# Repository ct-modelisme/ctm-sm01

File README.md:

# CTM-SM01: Servo-Motors decoder

The CTM-SM01 is a servo-motors electronic controller for modelrailway projects.
This electronic card is compatible with DCC & AC/DC train layouts.

## Licenses

The hardware is released under OpenHardware principes, and the software under OpenSource principes.

 - Hardware (PCB): [Creative Commons Attribution-ShareAlike 4.0 International License](http://creativecommons.org/licenses/by-sa/4.0/)
 - Software (Firmware): [GNU General Public License v3](https://www.gnu.org/licenses/)

## Current releases

 - Hardware (PCB): version 1.3
 - Software (Firmware): version 1.2

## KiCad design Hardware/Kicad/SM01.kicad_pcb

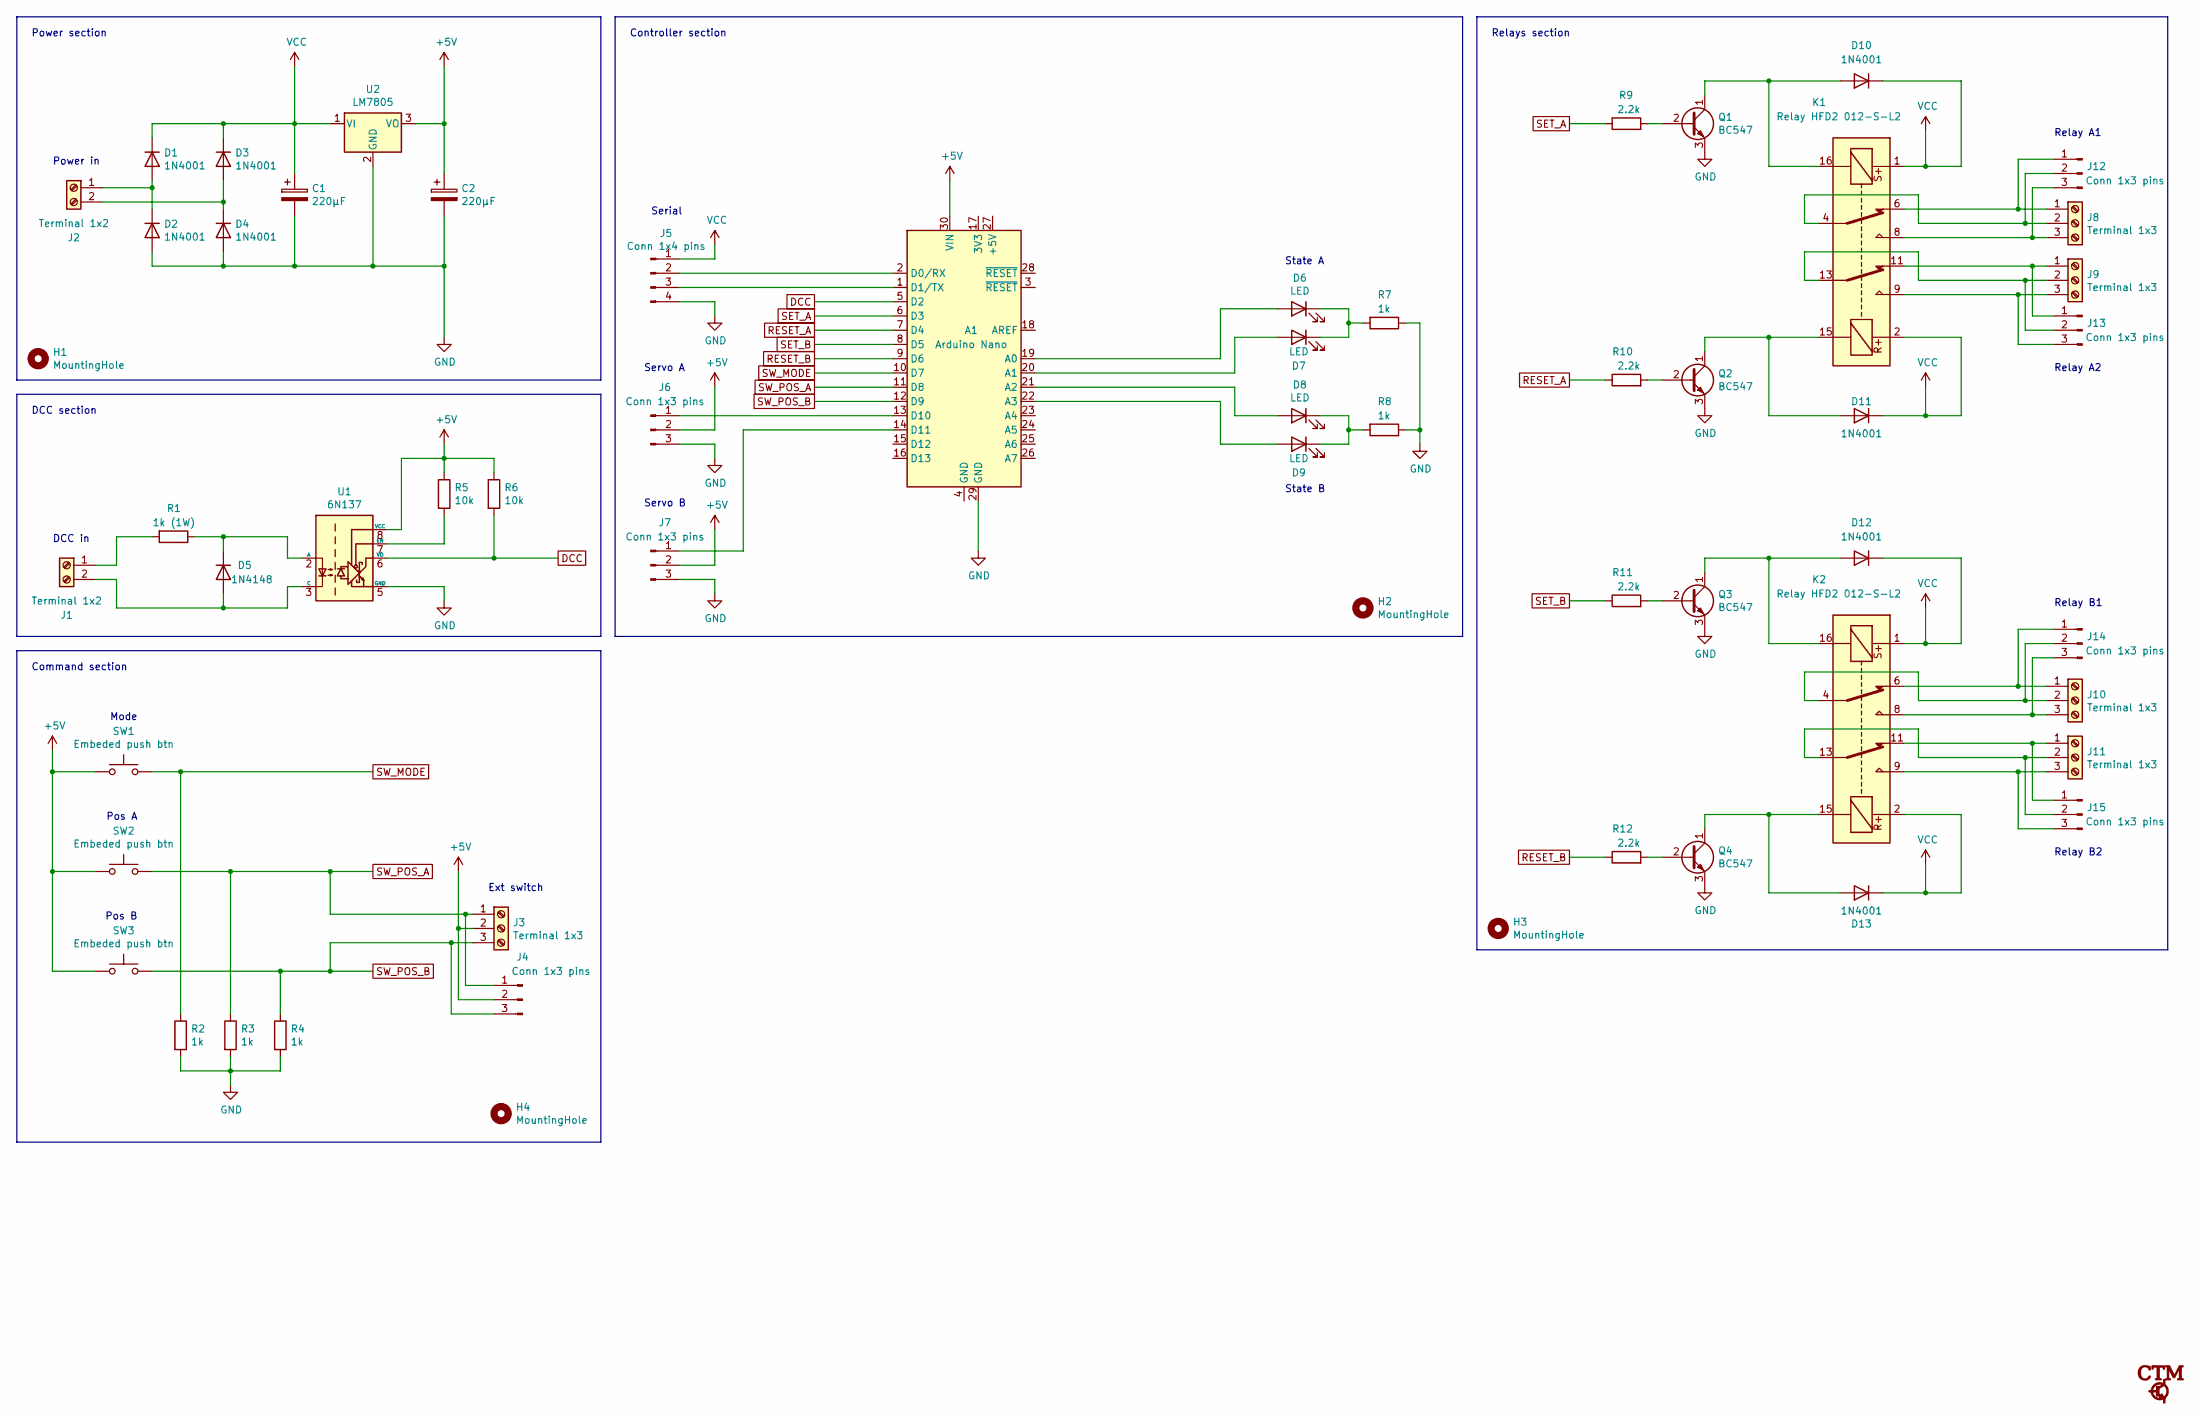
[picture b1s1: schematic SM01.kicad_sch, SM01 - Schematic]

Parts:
A1: Arduino Nano; Arduino_Nano
C1, C2: 220µF; CP_Radial_D6.3mm_P2.50mm
D1, D2, D3, D4, D10, D11, D12, D13: 1N4001; D_DO-41_SOD81_P10.16mm_Horizontal
D5: 1N4148; D_DO-35_SOD27_P7.62mm_Horizontal
D6, D7, D8, D9: LED; LED_D3.0mm
H1, H2, H3, H4: MountingHole; MountingHole_3.2mm_M3
J1, J2: Terminal 1x2; TerminalBlock_bornier-2_P5.08mm
J3, J8, J9, J10, J11: Terminal 1x3; TerminalBlock_bornier-3_P5.08mm
J4, J6, J7, J12, J13, J14, J15: Conn 1x3 pins; PinHeader_1x03_P2.54mm_Vertical
J5: Conn 1x4 pins; PinHeader_1x04_P2.54mm_Vertical
K1, K2: Relay HFD2 012-S-L2; DIP-16_W7.62mm_Socket
Q1, Q2, Q3, Q4: BC547; TO-92_Inline
R1: 1k (1W); R_Axial_DIN0309_L9.0mm_D3.2mm_P12.70mm_Horizontal
R2, R3, R4, R7, R8: 1k; R_Axial_DIN0207_L6.3mm_D2.5mm_P10.16mm_Horizontal
R5, R6: 10k; R_Axial_DIN0207_L6.3mm_D2.5mm_P10.16mm_Horizontal
R9, R10, R11, R12: 2.2k; R_Axial_DIN0207_L6.3mm_D2.5mm_P10.16mm_Horizontal
SW1, SW2, SW3: Embeded push btn; SW_PUSH_6mm
U1: 6N137; DIP-8_W7.62mm
U2: LM7805; TO-220-3_Vertical

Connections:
+5V: A1.30 (VIN), C2.1, J3.2, J4.2, J6.2, J7.2, R5.1, R6.1, SW1.1, SW2.1, SW3.1, U1.8 (VCC), U2.3 (VO)
DCC: A1.5 (D2), R6.2, U1.6 (VO)
GND: A1.29 (GND), C1.2, C2.2, D2.2 (A), D4.2 (A), J5.4, J6.3, J7.3, Q1.3 (E), Q2.3 (E), Q3.3 (E), Q4.3 (E), R2.2, R3.2, R4.2, R7.1, R8.1, U1.5 (GND), U2.2 (GND)
unnamed: A1.1 (D1/TX), J5.3
unnamed: A1.2 (D0/RX), J5.2
unnamed: A1.13 (D10), J6.1
unnamed: A1.14 (D11), J7.1
unnamed: A1.19 (A0), D6.2 (A)
unnamed: A1.20 (A1), D7.2 (A)
unnamed: A1.21 (A2), D8.2 (A)
unnamed: A1.22 (A3), D9.2 (A)
unnamed: D1.2 (A), D2.1 (K), J2.1
unnamed: D3.2 (A), D4.1 (K), J2.2
unnamed: D5.1 (K), R1.1, U1.2 (A)
unnamed: D5.2 (A), J1.2, U1.3 (C)
unnamed: D6.1 (K), D7.1 (K), R7.2
unnamed: D8.1 (K), D9.1 (K), R8.2
unnamed: D10.2 (A), K1.16, Q1.1 (C)
unnamed: D11.2 (A), K1.15, Q2.1 (C)
unnamed: D12.2 (A), K2.16, Q3.1 (C)
unnamed: D13.2 (A), K2.15, Q4.1 (C)
unnamed: J1.1, R1.2
unnamed: J10.1, J14.1, K2.6
unnamed: J10.2, J14.2, K2.4
unnamed: J10.3, J14.3, K2.8
unnamed: J11.1, J15.1, K2.11
unnamed: J11.2, J15.2, K2.13
unnamed: J11.3, J15.3, K2.9
unnamed: J8.1, J12.1, K1.6
unnamed: J8.2, J12.2, K1.4
unnamed: J8.3, J12.3, K1.8
unnamed: J9.1, J13.1, K1.11
unnamed: J9.2, J13.2, K1.13
unnamed: J9.3, J13.3, K1.9
unnamed: Q1.2 (B), R9.2
unnamed: Q2.2 (B), R10.2
unnamed: Q3.2 (B), R11.2
unnamed: Q4.2 (B), R12.2
unnamed: R5.2, U1.7 (EN)
RESET_A: A1.7 (D4), R10.1
RESET_B: A1.9 (D6), R12.1
SET_A: A1.6 (D3), R9.1
SET_B: A1.8 (D5), R11.1
SW_MODE: A1.10 (D7), R2.1, SW1.2
SW_POS_A: A1.11 (D8), J3.1, J4.1, R3.1, SW2.2
SW_POS_B: A1.12 (D9), J3.3, J4.3, R4.1, SW3.2
VCC: C1.1, D1.1 (K), D3.1 (K), D10.1 (K), D11.1 (K), D12.1 (K), D13.1 (K), J5.1, K1.1, K1.2, K2.1, K2.2, U2.1 (VI)

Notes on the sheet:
Relay B2
Command section
Power section
Relay B1
Pos B
Power in
Mode
Relay A2
Controller section
State A
State B
Servo A
DCC in
Relays section
Ext switch
Serial
Servo B
Pos A
Relay A1
DCC section

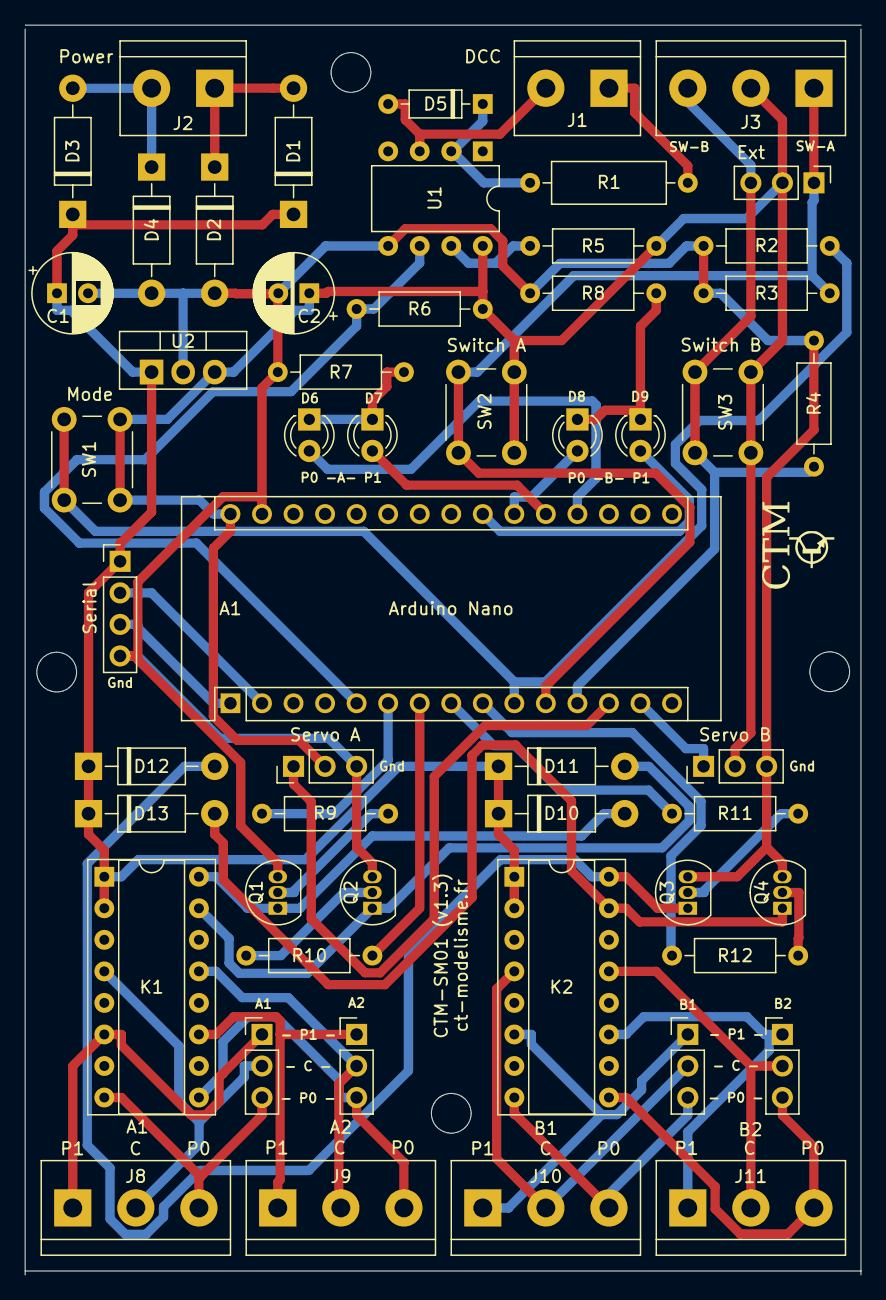
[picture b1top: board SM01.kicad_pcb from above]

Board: 2 copper layers, 67.3 x 100.6 mm, 58 parts (0 on the bottom side), 47 nets.

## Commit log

2023-08-07 Configure gitignore
2023-08-07 Prepare README for releasing
2023-08-07 Release hardware
2023-08-07 Release software
2023-08-07 Release documentation
2023-08-25 Add original documentation files
2023-08-25 Update documentation of pcb-1.3/firmware-1.2 version
2023-08-25 Allow office files
2023-08-25 Hotfix - Add original doc files
2024-02-17 Adding cartridge to PCB implementation

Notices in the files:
Hardware/Kicad/SM01.kicad_pcb:
All rights reserved
